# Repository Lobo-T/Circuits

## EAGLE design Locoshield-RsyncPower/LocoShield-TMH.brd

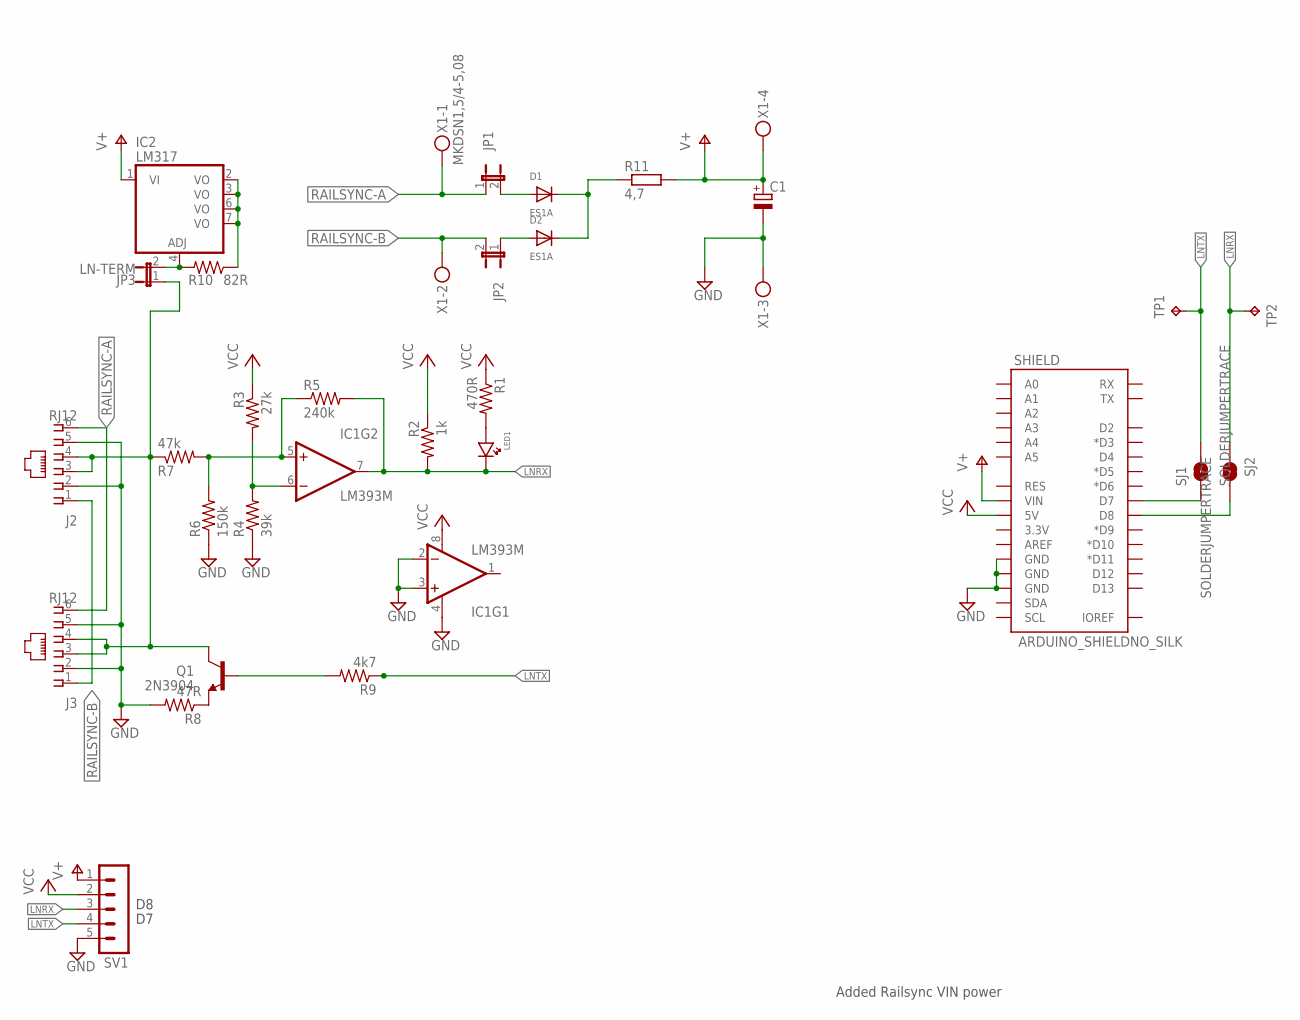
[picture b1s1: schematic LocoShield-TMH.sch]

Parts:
C1: CPOL-EUE2-5; E2-5
D1, D2: ES1A; SMADIODE
IC1: LM393M; SO08@1
IC2: LM317; SO08
J2, J3: RJ12; 520250-3
JP1, JP2: JUMPER-2PTH_LOCK; 1X02_LOCK
JP3: LN-TERM; 1X02_LOCK
LED1: LED0805-LED; 0805-LED
Q1: 2N3904; SOT23-3
R1: 470R; 0805-RES
R2: 1k; 0805-RES
R3: 27k; 0805-RES
R4: 39k; 0805-RES
R5: 240k; 0805-RES
R6: 150k; 0805-RES
R7: 47k; 0805-RES
R8: 47R; 0805-RES
R9: 4k7; 0805-RES
R10: 82R; 0805-RES
R11: 4,7; R1206
SHIELD: ARDUINO_SHIELDNO_SILK; DUEMILANOVE_VIAS
SJ1, SJ2: SOLDERJUMPERTRACE; SJ_2S-TRACE
SV1: MA05-1
TP1, TP2: TPPAD1-17; P1-17
X1: MKDSN1,5/4-5,08

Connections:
GND: C1.-, IC1.2 (-IN), IC1.3 (+IN), IC1.4 (V-), J2.2, J2.5, J3.2, J3.5, R4.1, R6.1, R8.2, SHIELD.GND@0 (GND), SHIELD.GND@1 (GND), SHIELD.GND@2 (GND), SV1.5, X1.3
LNRX: IC1.7 (OUT), LED1.C, R2.2, R5.2, SJ2.1, SV1.3, TP2.TP
LNTX: R9.1, SJ1.2, SV1.4, TP1.TP
LOCONET: J2.3, J2.4, J3.3, J3.4, JP3.1, Q1.3 (C), R7.1
unnamed: Q1.1 (B), R9.2
unnamed: IC1.5 (+IN), R5.1, R6.2, R7.2
unnamed: D1.A, JP1.2
unnamed: D2.A, JP2.1
unnamed: IC1.6 (-IN), R3.2, R4.2
unnamed: Q1.2 (E), R8.1
unnamed: SHIELD.D8, SJ2.2
unnamed: SHIELD.D7, SJ1.1
unnamed: D1.C, D2.C, R11.1
unnamed: LED1.A, R1.2
unnamed: IC2.4 (ADJ), JP3.2, R10.2
RAILSYNC-A: J2.6, J3.6, JP1.1, X1.1
RAILSYNC-B: J2.1, J3.1, JP2.2, X1.2
V+: C1.+, IC2.1 (VI), R11.2, SHIELD.VIN, SV1.1, X1.4
VCC: IC1.8 (V+), R1.1, R2.1, R3.1, SHIELD.5V, SV1.2
VOUT: IC2.2 (VO), IC2.3 (VO), IC2.6 (VO), IC2.7 (VO), R10.1

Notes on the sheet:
Added Railsync VIN power

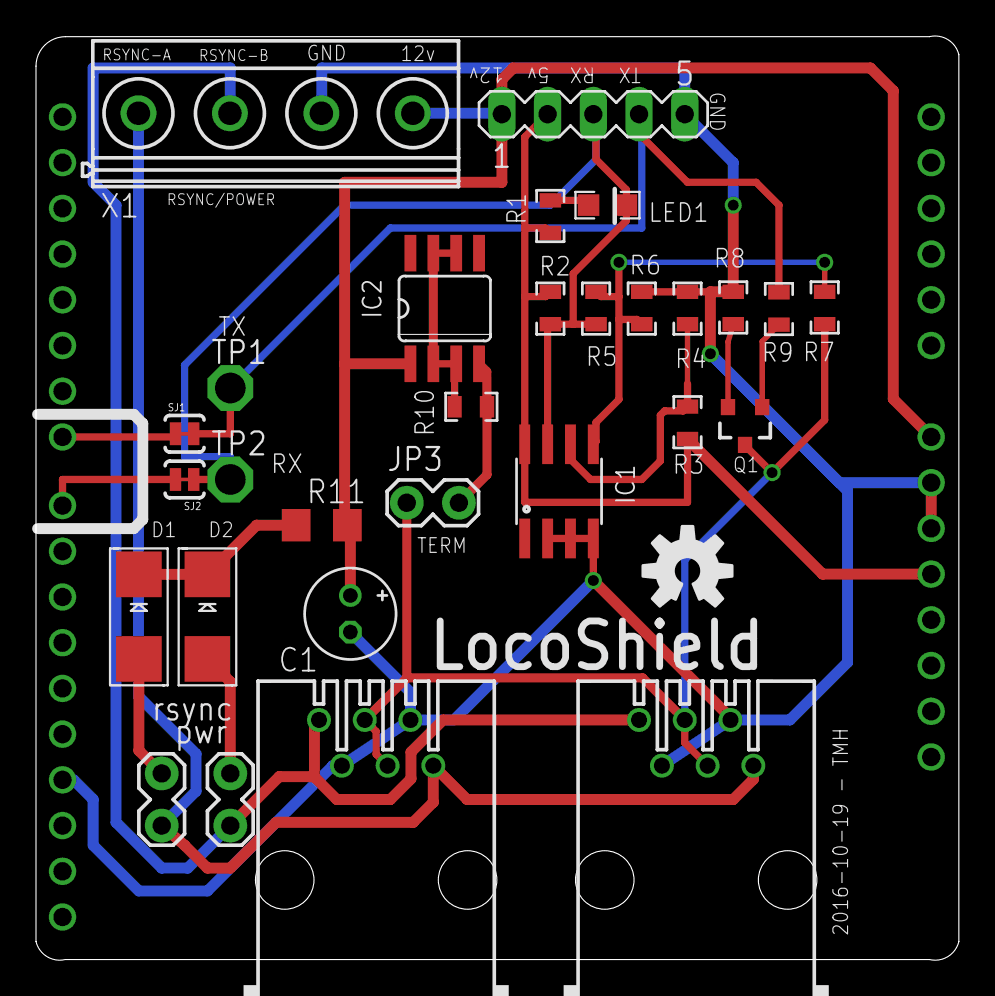
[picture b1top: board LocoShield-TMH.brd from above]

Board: 2 copper layers, 51.3 x 51.3 mm, 31 parts (0 on the bottom side), 20 nets.

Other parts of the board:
U$1: OSHW-LOGOM; OSHW-LOGO-M

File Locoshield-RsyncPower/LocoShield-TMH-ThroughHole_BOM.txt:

Partlist exported from C:/Users/Trond/Documents/eagle/Locoshield Rsync power/LocoShield-TMH-ThroughHole.sch at 22.10.2016 22:28

Part   Value                 Device                Package          Description                          ELFA       MF MPN OC_FARNELL OC_NEWARK TP_SIGNAL_NAME
C1                           CPOL-EUE2-5           E2-5             POLARIZED CAPACITOR, European symbol                                                      
D1     UF4004                1N4148DO35-7          DO35-7           DIODE                                170-02-221                                           
D2     UF4004                1N4148DO35-7          DO35-7           DIODE                                170-02-221                                           
IC1    LM393N                LM393N                DIL08            COMPARATOR                           300-19-446                                           
IC2    LM317LZ               LM317LZ               TO92             Positive VOLTAGE REGULATOR           173-12-085                                           
J2     RJ12                  520250-3              520250-3         AMP connector                        42-688-27                                            
J3     RJ12                  520250-3              520250-3         AMP connector                        42-688-27                                            
JP1                          JUMPER-2PTH_LOCK      1X02_LOCK        Jumper                               124-50-887                                           
JP2                          JUMPER-2PTH_LOCK      1X02_LOCK        Jumper                               124-50-887                                           
JP3    LN-TERM               JUMPER-2PTH_LOCK      1X02_LOCK        Jumper                               124-50-887                                           
LED1                         LED3MM                LED3MM           LED                                  175-01-530                                           
Q1     2N3904                2N3904                TO92             NPN TRANSISTOR                       171-30-038                                           
R1     470R                  R-EU_0207/10          0207/10          RESISTOR, European symbol            160-59-206                                           
R2     1k                    R-EU_0207/10          0207/10          RESISTOR, European symbol            160-59-214                                           
R3     27k                   R-EU_0207/10          0207/10          RESISTOR, European symbol            160-59-253                                           
R4     39k                   R-EU_0207/10          0207/10          RESISTOR, European symbol            160-59-257                                           
R5     240k                  R-EU_0207/10          0207/10          RESISTOR, European symbol            160-59-277                                           
R6     150k                  R-EU_0207/10          0207/10          RESISTOR, European symbol            160-59-271                                           
R7     47k                   R-EU_0207/10          0207/10          RESISTOR, European symbol            160-59-259                                           
R8     47R                   R-EU_0207/10          0207/10          RESISTOR, European symbol            160-59-181                                           
R9     4k7                   R-EU_0207/10          0207/10          RESISTOR, European symbol            160-73-043                                           
R10    82R                   R-EU_0207/10          0207/10          RESISTOR, European symbol            160-59-187                                           
R11    4,7                   R-EU_0207/10          0207/10          RESISTOR, European symbol            160-59-157                                           
SHIELD ARDUINO_SHIELDNO_SILK ARDUINO_SHIELDNO_SILK DUEMILANOVE_VIAS                                                                                           
SJ1    SOLDERJUMPERTRACE     SOLDERJUMPERTRACE     SJ_2S-TRACE      Solder Jumper                                                                             
SJ2    SOLDERJUMPERTRACE     SOLDERJUMPERTRACE     SJ_2S-TRACE      Solder Jumper                                                                             
SV1                          MA05-1                MA05-1           PIN HEADER                           143-00-499        unknown    unknown                 
TP1    TPPAD1-17             TPPAD1-17             P1-17            Test pad                                                                                  
TP2    TPPAD1-17             TPPAD1-17             P1-17            Test pad                                                                                  
X1     MKDSN1,5/2-5,08       MKDSN1,5/2-5,08       MKDSN1,5/2-5,08  MKDSN 1,5/ 2-5,08 Printklemme        148-45-038                                           
X2     MKDSN1,5/2-5,08       MKDSN1,5/2-5,08       MKDSN1,5/2-5,08  MKDSN 1,5/ 2-5,08 Printklemme        148-45-038

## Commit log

2016-10-22 Deleliste
2021-01-23 Add files via upload
    Raspberry Pi Pico Eagle library
2021-01-24 Add files via upload
    Flyttet navn og pinne en indikator slik at de ikke havner utenfor kortet når du plasserer Picoen ved enden av kortet slik at USB kontakten stikker utenfor.
2021-01-26 Add files via upload
    Flyttet navn
2021-01-26 Add files via upload
    Kastellasjoner lagt til.
2021-01-26 Add files via upload
    Endret lengde.

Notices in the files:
parts and their libraries:
SparkFun-Retired: Licensing:Creative Commons ShareAlike 4.0 International - https://creativecommons.org/licenses/by-sa/4.0
